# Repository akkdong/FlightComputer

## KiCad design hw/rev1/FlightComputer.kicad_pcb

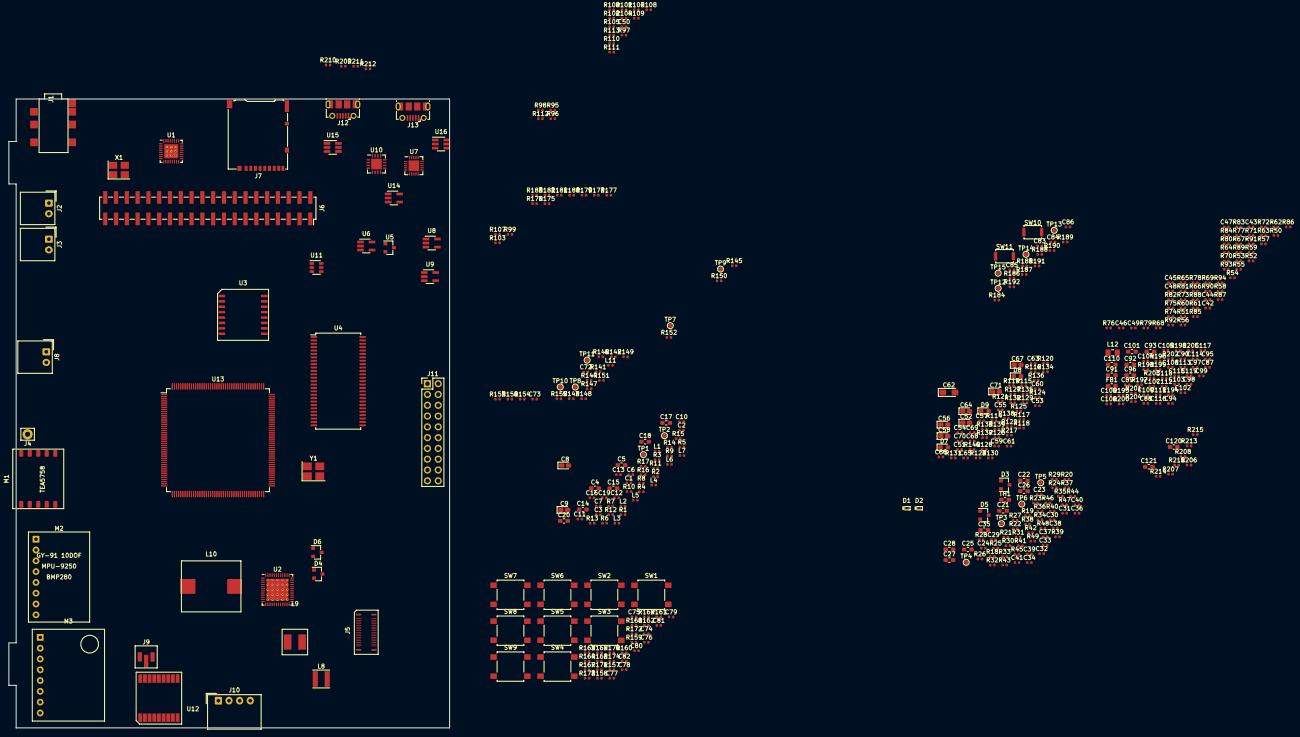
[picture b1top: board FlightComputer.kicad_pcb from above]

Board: 2 copper layers, 103.7 x 148.0 mm, 421 parts (0 on the bottom side), 380 nets, no tracks yet.

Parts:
C1, C2, C3, C16, C19, C41, C42, C43, C44, C45, C46, C47, C48, C49, C50, C51, C57, C63, C68, C70, C73, C74, C75, C76, C77, C78, C79, C80, C81, C82, C85, C86, C87, C88, C89, C94, C98, C100, C102, C103, C104, C105, C106, C107, C108, C109, C111, C112, C113, C114, C115, C116, C117, C118, C119: 0.1uF; C_0402_1005Metric
C4, C5, C14, C15, C91, C92, C93, C110: 4.7uF; C_0603_1608Metric_Pad1.05x0.95mm_HandSolder
C6, C7, C10, C11, C12, C13, C95: 220pF; C_0402_1005Metric
C8, C9, C52, C56, C58, C64, C67, C71: 10uF; CP_EIA-1608-08_AVX-J_Pad1.25x1.05mm_HandSolder
C17, C18, C20, C21, C22, C35, C96, C101, C120, C121: 10uF; C_0603_1608Metric_Pad1.05x0.95mm_HandSolder
C23, C24, C31, C32, C33, C34, C36, C37, C38, C39: 4.7uF; C_0402_1005Metric
C25, C26: 0.1uF; C_0603_1608Metric_Pad1.05x0.95mm_HandSolder
C27, C28: 0.01uF; C_0603_1608Metric_Pad1.05x0.95mm_HandSolder
C29, C30, C61: 2.2uF; C_0402_1005Metric
C40, C53, C54, C59, C65, C69, C90, C97, C99: 1uF; C_0402_1005Metric
C55, C60, C66: N/C; C_0402_1005Metric
C62: 100uF; CP_EIA-3216-10_Kemet-I_Pad1.58x1.35mm_HandSolder
C72: 22pF; C_0402_1005Metric
C83, C84: 18pF; C_0402_1005Metric
D1, D2: BAS3010S; TSLP-2-17
D3, D4, D5, D6: BAT54-SOT23; D_SOT-23_ANK
D7: LED_R; LED_0603_1608Metric_Pad1.05x0.95mm_HandSolder
D8, D9: LED_G; LED_0603_1608Metric_Pad1.05x0.95mm_HandSolder
FB1: BEAD(BMJ1608HM180NTR); L_0603_1608Metric_Pad1.05x0.95mm_HandSolder
J1: SJ-43617-SMT
J2, J3, J8: Conn_01x02; Molex_SPOX_5268-02A_1x02_P2.50mm_Horizontal
J4: Conn_01x01; Pin_D1.2mm_L10.2mm_W2.9mm_FlatFork
J5: ED060SC7_EPD; AXT334124
J6: RPI_Connector; PinSocket_2x20_P2.54mm_Vertical_SMD
J7: Micro_SD_Card; microSD_HC_Hirose_DM3AT-SF-PEJM5
J9: IPEX_IPX; IPEX-IPX
J10: Conn_DEBUG; Molex_SPOX_5268-04A_1x04_P2.50mm_Horizontal
J11: Conn_02x10_Odd_Even; PinHeader_2x10_P2.54mm_Vertical
J12, J13: USB_B_Micro; USB_Micro-B_Molex-105017-0001
L1, L2, L3, L4, L5, L6, L7: Ferrite; L_0402_1005Metric
L8: 2.2uH; L_Taiyo-Yuden_MD-4040
L9: 4.7uH; L_1515(4040 metric)
L10: 68uH w/2A; L_10x11mm
L11: 33nH; L_0402_1005Metric
L12: 2.2uH (LQM2MPN2R2NG0); L_0806_2016Metric
M1: TEA5767_Radio_Module; TEA5756-TJ-102BC
M2: GY-91
M3: GY-86
R1, R113, R116, R120, R123, R127, R133, R136, R161, R162, R163, R164, R169, R170, R171, R172, R174, R175, R176, R183, R186, R188: 100K; R_0402_1005Metric
R2, R3, R4, R5, R6, R7, R8, R9, R10, R13, R15, R16, R17, R23, R24, R25, R26, R27, R28, R29, R32, R33, R34, R35, R38, R39, R40, R41, R42, R43, R44, R45, R47, R48, R49, R50, R51, R52, R53, R54, R55, R56, R57, R58, R59, R60, R61, R62, R63, R64, R65, R66, R67, R68, R69, R70, R71, R72, R73, R74, R75, R76, R77, R78, R79, R80, R81, R82, R83, R84, R85, R86, R87, R88, R89, R90, R91, R92, R93, R94, R97, R98, R99, R100, R101, R102, R107, R108, R109, R110, R111, R112, R122, R124, R126, R131, R135, R141, R142, R143, R144, R145, R146, R147, R150, R151, R152, R153, R154, R155, R156, R177, R178, R179, R180, R181, R182, R206, R209, R210, R211, R212, R213, R214, R215, R216: 33R; R_0402_1005Metric
R11, R12, R117, R148, R149, R185, R193, R195, R198, R199, R200: N/C; R_0402_1005Metric
R14, R30, R31, R36, R37, R46, R184, R189, R190, R191, R192, R207: 10K; R_0402_1005Metric
R18, R20, R115, R128, R140: 1M; R_0402_1005Metric
R19: 47.5K; R_0402_1005Metric
R21: 52.3K; R_0402_1005Metric
R22: 43K; R_0402_1005Metric
R95, R96, R103, R104, R105, R106: 47K; R_0402_1005Metric
R114: 270K; R_0402_1005Metric
R118, R119, R134, R138, R157, R158, R159, R160, R165, R166, R167, R168, R173, R187, R217: 1K; R_0402_1005Metric
R121: 15K; R_0402_1005Metric
R125, R129: 1.87M; R_0402_1005Metric
R130, R132: 340K; R_0402_1005Metric
R137: 560K; R_0402_1005Metric
R139, R194, R196, R197, R201, R202, R203, R204, R205: 0R; R_0402_1005Metric
R208: 47k; R_0402_1005Metric
SW1, SW2, SW3, SW4, SW5, SW6, SW7, SW8, SW9: SW_Push; SW_SPST_B3S-1000
SW10, SW11: SW_Push; SW_Push_SPST_NO_Alps_SKRK
TH1: NCP18XH103F03RB(10K); R_0603_1608Metric_Pad1.05x0.95mm_HandSolder
TP1: OUT3; TestPoint_Pad_D1.0mm
TP2: RINPUT3; TestPoint_Pad_D1.0mm
TP3: EINK_SPI_SCL; TestPoint_Pad_D1.0mm
TP4: EINK_SPI_SDI; TestPoint_Pad_D1.0mm
TP5: EINK_SPI_CS; TestPoint_Pad_D1.0mm
TP6: EINK_SPI_SDO; TestPoint_Pad_D1.0mm
TP7: GPS_SCL; TestPoint_Pad_D1.0mm
TP8: GPS_nRST; TestPoint_Pad_D1.0mm
TP9: GPS_SDA; TestPoint_Pad_D1.0mm
TP10: GPS_WAKEUP; TestPoint_Pad_D1.0mm
TP11: 1PPS; TestPoint_Pad_D1.0mm
TP12: PA1; TestPoint_Pad_D1.0mm
TP13: PC2; TestPoint_Pad_D1.0mm
TP14: PC14; TestPoint_Pad_D1.0mm
TP15: PC15; TestPoint_Pad_D1.0mm
U1: WM8960; QFN-32-1EP_5x5mm_P0.5mm_EP3.3x3.3mm_ThermalVias
U2: TPS65186; VQFN-48-1EP_7x7mm_P0.5mm_EP5.15x5.15mm_ThermalVias
U3: MT25QL512ABB8ESF; SOP2-16_7.5x10.3mm_P1.27mm
U4: MT48LC16M16A2P; TSOP-II-54_22.2x10.16mm_P0.8mm
U5: MAX809TTRG; SOT-23
U6, U8, U9: XC6220B331MR-G; SOT-23-5_HandSoldering
U7: MCP73871; QFN-20-1EP_4x4mm_P0.5mm_EP2.5x2.5mm
U10: TPS61090; QFN-16-1EP_4x4mm_P0.65mm_EP2.5x2.5mm
U11: TPS22917DBV; SOT-23-6
U12: Teseo-LIV3F
U13: STM32H745IIT; LQFP-176_24x24mm_P0.5mm
U14: STMPS2151STR; SOT-23-5_HandSoldering
U15, U16: USBLC6-2SC6; SOT-23-6_Handsoldering
X1: 24MHz; Oscillator_SMD_Abracon_ASE-4Pin_3.2x2.5mm_HandSoldering
Y1: 25MHz; Crystal_SMD_3225-4Pin_3.2x2.5mm_HandSoldering

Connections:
+15V: C33.1, J5.2, J5.4, U2.44
+22V: C29.2, D3.1, J5.25, R18.1
+BATT: C56.1, J8.1, U7.14, U7.15, U7.16
-15V: C34.2, J5.1, J5.3, U2.3
-20V: C30.1, D6.2, J5.27, J5.29, R20.2
/Codec/HPDETECT: J1.4, R9.2
/Codec/I2C_SCL: J6.5, R7.2, R17.2, R96.2
/Codec/I2C_SDA: J6.3, R8.2, R16.2, R95.2
/Codec/I2S_DIN: J6.40, R5.2
/Codec/I2S_LRCK: J6.35, R4.2
/Codec/I2S_MCLK: R2.2, R15.2
/Codec/I2S_SCLK: J6.12, R3.2
/Codec/RADIO_L: C18.2, R10.2, R11.2
/Codec/RADIO_R: C17.2, R12.2, R13.2
/DEBUG/DEBUG_JMS-SWDIO: R179.1, U13.132
/DEBUG/DEBUG_JTCK-SWCLK: R180.1, R183.1, U13.138
/DEBUG/DEBUG_JTDI: R175.2, R178.1, U13.139
/DEBUG/DEBUG_JTDO-SWO: R181.1, U13.162
/DEBUG/DEBUG_nJTRST: R176.2, R177.1, U13.163
/DEBUG/nRST: C85.1, R182.1, R186.1, SW10.1, U13.33
/EINK-PMIC/EPD_CKV: R48.2, U13.101
/EINK-PMIC/EPD_CL: R32.1, U13.102
/EINK-PMIC/EPD_D0: R38.1, U13.145
/EINK-PMIC/EPD_D1: R39.2, U13.146
/EINK-PMIC/EPD_D2: R40.1, U13.147
/EINK-PMIC/EPD_D3: R41.2, U13.148
/EINK-PMIC/EPD_D4: R42.1, U13.149
/EINK-PMIC/EPD_D5: R43.2, U13.150
/EINK-PMIC/EPD_D6: R44.1, U13.94
/EINK-PMIC/EPD_D7: R45.2, U13.95
/EINK-PMIC/EPD_GMODE: R47.2, U13.103
/EINK-PMIC/EPD_LE: R33.2, U13.104
/EINK-PMIC/EPD_OE: R34.1, U13.107
/EINK-PMIC/EPD_PMIC_PWRUP: R26.1, U13.155
/EINK-PMIC/EPD_PMIC_PWR_GOOD: R29.2, U13.156
/EINK-PMIC/EPD_PMIC_SCL: R25.1, R189.2, U13.168
/EINK-PMIC/EPD_PMIC_SDA: R24.1, R190.2, U13.166
/EINK-PMIC/EPD_PMIC_VCOM: R23.1, U13.153
/EINK-PMIC/EPD_PMIC_WAKEUP: R27.1, U13.154
/EINK-PMIC/EPD_PMIC_nINT: R28.2, U13.157
/EINK-PMIC/EPD_SPH: R35.2, U13.108
/EINK-PMIC/EPD_SPV: R49.2, U13.109
/EINK-PMIC/VCOM: C36.1, J5.21, J5.23, U2.14
/EINK_MISO: R100.2, U13.51
/EINK_MOSI: R99.2, U13.52
/EINK_SCLK: R101.2, U13.50
/EINK_nCS: R102.1, U13.49
/IMU1_MISO: R143.2, U13.4
/IMU1_MOSI: R142.2, U13.5
/IMU1_SCLK: R141.2, U13.1
/IMU1_nCS1: R144.2, U13.2
/IMU1_nCS2: R145.2, U13.3
/IMU2_DRDY: R154.2, U13.55
/IMU2_FSYNC: R152.2, U13.56
/IMU2_SCL: R148.1, R150.2, R191.2, U13.78
/IMU2_SDA: R149.1, R151.2, R192.2, U13.79
/IMU2_nINT: R153.2, U13.57
/KEYBOARD/KEY_DOWN: R158.2, U13.123
/KEYBOARD/KEY_ENTER: R165.2, U13.41
/KEYBOARD/KEY_ESCAPE: R166.2, U13.9
/KEYBOARD/KEY_FUNC1: R167.2, U13.124
/KEYBOARD/KEY_FUNC2: R168.2, U13.125
/KEYBOARD/KEY_LEFT: R159.2, U13.53
/KEYBOARD/KEY_RIGHT: R160.2, U13.54
/KEYBOARD/KEY_UP: R157.2, U13.122
/MCU/BAT_SENSING: R139.1, U13.37
/MCU/BOOT0: C86.1, R188.2, SW11.1, U13.167
/MCU/FMC_A0: R51.2, U13.18
/MCU/FMC_A1: R53.2, U13.19
/MCU/FMC_A2: R55.2, U13.20
/MCU/FMC_A3: R57.2, U13.21
/MCU/FMC_A4: R59.2, U13.22
/MCU/FMC_A5: R61.2, U13.23
/MCU/FMC_A6: R63.2, U13.59
/MCU/FMC_A7: R65.2, U13.60
/MCU/FMC_A8: R68.2, U13.61
/MCU/FMC_A9: R71.2, U13.62
/MCU/FMC_A10: R74.2, U13.63
/MCU/FMC_A11: R78.2, U13.66
/MCU/FMC_A12: R81.2, U13.110
/MCU/FMC_BA0: R85.2, U13.114
/MCU/FMC_BA1: R86.2, U13.115
/MCU/FMC_CKE1: R94.2, U13.164
/MCU/FMC_CLK: R93.2, U13.118
/MCU/FMC_D0: R50.1, U13.97
/MCU/FMC_D1: R52.1, U13.98
/MCU/FMC_D2: R54.1, U13.143
/MCU/FMC_D3: R56.1, U13.144
/MCU/FMC_D4: R58.1, U13.67
/MCU/FMC_D5: R60.1, U13.68
/MCU/FMC_D6: R62.1, U13.69
/MCU/FMC_D7: R64.1, U13.72
/MCU/FMC_D8: R67.1, U13.73
/MCU/FMC_D9: R70.1, U13.74
/MCU/FMC_D10: R73.1, U13.75
/MCU/FMC_D11: R77.1, U13.76
/MCU/FMC_D12: R80.1, U13.77
/MCU/FMC_D13: R82.1, U13.89
/MCU/FMC_D14: R83.1, U13.90
/MCU/FMC_D15: R84.1, U13.91
/MCU/FMC_nBL0: R87.2, U13.170
/MCU/FMC_nBL1: R88.2, U13.171
/MCU/FMC_nCAS: R90.2, U13.161
/MCU/FMC_nE1: R92.2, U13.165
/MCU/FMC_nRAS: R91.2, U13.58
/MCU/FMC_nWE: R89.2, U13.34
/MCU/LOW_BATTERY: R131.2, U13.35
/MCU/PWR_5V_EN: R124.1, U13.169
/MCU/PWR_BAT+_EN: R135.1, U13.111
/MCU/PWR_EXTRA_EN: R126.2, U13.158
/MCU/PWR_PERIPH_EN: R122.2, U13.117
/MCU/USB_FS_DN: R216.1, U13.130
/MCU/USB_FS_DP: R215.1, U13.131
/MCU/USB_FS_VBUS: R214.1, U13.142
/MCU/USB_HS_DN: R212.1, U13.87
/MCU/USB_HS_DP: R211.1, U13.88
/MCU/USB_HS_ID: R213.1, U13.85
/MCU/USB_HS_OVCR: R209.1, U13.127
/MCU/USB_HS_PWR_EN: R206.1, U13.96
/MCU/USB_HS_VBUS: R210.1, U13.86
/Memory/NOR_CLK: R79.1, U13.30
/Memory/NOR_DQ0: R66.2, U13.28
/Memory/NOR_DQ1: R69.2, U13.29
/Memory/NOR_DQ2: R72.2, U13.27
/Memory/NOR_DQ3: R76.2, U13.26
/Memory/NOR_nCS: R75.1, U13.116
/Raspberry/I2S_DIN: J6.38, R6.2
/Raspberry/SDIO_CLK: J6.15, R110.2
/Raspberry/SDIO_CMD: J6.16, R104.2, R109.2
/Raspberry/SDIO_DAT0: J6.18, R105.2, R111.2
/Raspberry/SDIO_DAT1: J6.22, R106.2, R112.2
/Raspberry/SDIO_DAT2: J6.37, R103.2, R107.2
/Raspberry/SDIO_DAT3: J6.13, R108.2, R113.1
/VARIO_RX: R97.1, U13.141
/VARIO_TX: R98.1, U13.140
/Vario/EXTERNAL_RX: R155.2, U13.128
/Vario/EXTERNAL_TX: R156.2, U13.129
/Vario/GPS_RX: R147.1, U13.43
/Vario/GPS_TX: R146.1, U13.46
GND: C1.2, C2.2, C3.2, C4.2, C5.2, C6.2, C7.2, C10.2, C11.2, C12.2, C13.2, C14.2, C15.1, C16.1, C19.2, C20.2, C21.2, C22.1, C23.2, C24.1, C25.2, C26.1, C29.1, C30.2, C31.2, C32.1, C33.2, C34.1, C35.2, C36.2, C37.1, C38.1, C39.1, C40.2, C41.2, C42.2, C43.1, C44.1, C45.1, C46.1, C47.1, C48.1, C49.1, C50.1, C51.2, C52.2, C53.2, C54.2, C55.2, C56.2, C57.2, C58.2, C59.2, C60.2, C61.2, C62.2, C63.2, C64.2, C65.2, C66.2, C67.2, C68.2, C69.2, C70.2, C71.2, C72.1, C73.1, C74.2, C75.2, C76.2, C77.2, C78.2, C79.2, C80.2, C81.2, C82.2, C83.2, C84.2, C85.2, C86.2, C87.2, C88.2, C89.2, C90.2, C94.2, C102.2, C103.2, C104.2, C105.2, C106.2, C107.2, C108.2, C109.2, C110.2, C111.2, C112.2, C113.2, C114.2, C115.2, C116.2, C117.2, C118.2, C119.2, C120.2, C121.2, D9.1, J1.1, J5.6, J5.8, J5.31, J5.32, J6.6, J6.9, J6.14, J6.20, J6.25, J6.30, J6.34, J6.39, J7.6, J8.2, J9.2, J9.3, J10.4, J11.4, J11.6, J11.8, J11.10, J11.12, J11.14, J11.16, J11.18, J11.20, J12.5, J12.6, J13.5, J13.6, L9.2, M1.3, M1.6, M1.9, M2.3, M3.3, R19.1, R21.2, R22.1, R113.2, R116.2, R119.2, R120.2, R121.2, R123.1, R127.1, R130.2, R132.2, R133.2, R136.1, R140.1, R161.1, R162.1, R163.1, R164.1, R169.1, R170.1, R171.1, R172.1, R174.1, R183.2, R185.1, R188.1, R204.2, R205.2, R207.2, SW10.2, TH1.2, U1.9, U1.20, U1.24, U1.28, U1.33, U2.6, U2.8, U2.33, U2.41, U2.48, U3.10, U4.6, U4.12, U4.28, U4.41, U4.46, U4.52, U4.54, U5.1, U6.2, U7.10, U7.11, U7.21, U8.2, U9.2, U10.5, U10.6, U10.7, U10.10, U10.13, U10.17, U11.2, U12.1, U12.10, U12.12, U14.2, U15.2, U16.2, X1.2
GNDS: C91.1, C92.1, C93.1, C95.2, C96.2, C101.2, R205.1, U13.6, U13.12, U13.14, U13.24, U13.45, U13.47, U13.64, U13.70, U13.81, U13.83, U13.93, U13.100, U13.106, U13.112, U13.119, U13.134, U13.137, U13.151, U13.159, U13.173
unnamed: C6.1, J1.2, L1.2
unnamed: C7.1, J1.3, L2.2
unnamed: C8.1, U1.31
unnamed: C8.2, L1.1
unnamed: C9.1, U1.29
unnamed: C9.2, L2.1
unnamed: C10.1, J2.1, L3.2
unnamed: C11.1, J2.2, L4.2
unnamed: C12.1, J3.1, L5.2
unnamed: C13.1, J3.2, L6.2
unnamed: C14.1, U1.1
unnamed: C15.2, U1.27
unnamed: C16.2, R14.1, X1.1
unnamed: C17.1, M1.8
unnamed: C18.1, M1.7
unnamed: C19.1, C20.1, L7.2, M1.5
unnamed: C23.1, C31.1, D1.1, U2.37, U2.42, U2.43
unnamed: C24.2, C32.2, C39.2, D2.2, U2.4, U2.16, U2.23, U2.28, U2.29, U2.49
unnamed: C25.1, D4.2, U2.35
unnamed: C26.2, D5.1, U2.31
unnamed: C27.1, U2.36
unnamed: C27.2, D3.2, D4.1
unnamed: C28.1, D5.2, D6.1
unnamed: C28.2, U2.30
unnamed: C37.2, U2.7
unnamed: C38.2, U2.1
unnamed: C53.1, R115.1, U6.3
unnamed: C55.1, U6.4
unnamed: C60.1, U8.4
unnamed: C66.1, U9.4
unnamed: C72.2, L11.1, U12.14
unnamed: C74.1, R157.1, R161.2, SW1.1
unnamed: C75.1, R158.1, R162.2, SW2.1
unnamed: C76.1, R159.1, R163.2, SW3.1
unnamed: C77.1, R160.1, R164.2, SW4.1
unnamed: C78.1, R165.1, R169.2, SW5.1
unnamed: C79.1, R166.1, R170.2, SW6.1
unnamed: C80.1, R167.1, R171.2, SW7.1
unnamed: C81.1, R168.1, R172.2, SW8.1
unnamed: C82.1, R173.1, R174.2, SW9.2
unnamed: C83.1, U13.31, Y1.3
unnamed: C84.1, U13.32, Y1.1
unnamed: C87.1, R195.1
unnamed: C88.1, R196.1
unnamed: C89.1, R197.1
unnamed: C91.2, C92.2, C93.2, L12.1, R194.1, R198.1, R199.1, R200.1, R203.2, U13.17
unnamed: C95.1, L12.2, U13.15
unnamed: C96.1, FB1.2, R193.1, U13.16
unnamed: C97.1, C98.1, R201.1, U13.40
unnamed: C99.1, C100.1, R202.1, U13.39
unnamed: C97.2, C98.2, C99.2, C100.2, R204.1, U13.38
unnamed: C101.1, R203.1
unnamed: C120.1, J12.1, R210.2, U14.1, U15.5
unnamed: D1.2, L8.2, U2.40
unnamed: D2.1, L9.1, U2.25
unnamed: D7.1, R117.1, R217.1
unnamed: D8.1, R118.1
unnamed: D9.2, R138.2
unnamed: J1.12, R1.2
unnamed: J4.1, M1.10
unnamed: J5.9, R32.2
unnamed: J5.10, R33.1
unnamed: J5.11, R34.2
unnamed: J5.12, R35.1
unnamed: J5.13, R38.2
unnamed: J5.14, R39.1
unnamed: J5.15, R40.2
unnamed: J5.16, R41.1
unnamed: J5.17, R42.2
unnamed: J5.18, R43.1
unnamed: J5.19, R44.2
unnamed: J5.20, R45.1
unnamed: J5.22, R36.2, TP3.1
unnamed: J5.24, R37.2, TP4.1
unnamed: J5.26, R47.1
unnamed: J5.28, R48.1
unnamed: J5.30, R49.1
unnamed: J5.33, R46.2, TP5.1
unnamed: J5.34, TP6.1
unnamed: J6.8, R97.2
unnamed: J6.10, R98.2
unnamed: J6.19, R99.1
unnamed: J6.21, R100.1
unnamed: J6.23, R101.1
unnamed: J6.24, R102.2
unnamed: J7.1, R107.1
unnamed: J7.2, R108.1
unnamed: J7.3, R109.1
unnamed: J7.5, R110.1
unnamed: J7.7, R111.1
unnamed: J7.8, R112.1
unnamed: J9.1, L11.2, U12.11
unnamed: J10.2, R155.1
unnamed: J10.3, R156.1
unnamed: J11.3, R177.2
unnamed: J11.5, R178.2
unnamed: J11.7, R179.2
unnamed: J11.9, R180.2
unnamed: J11.13, R181.2
unnamed: J11.15, R182.2
unnamed: J12.2, U15.1
unnamed: J12.3, U15.3
unnamed: J12.4, R213.2
unnamed: J13.2, U16.1
unnamed: J13.3, U16.3
unnamed: L3.1, U1.25
unnamed: L4.1, U1.23
unnamed: L5.1, U1.22
unnamed: L6.1, U1.19
unnamed: L10.2, U10.3, U10.4
unnamed: M1.1, R16.1
unnamed: M1.2, R17.1
unnamed: M2.4, R141.1, R148.2
unnamed: M2.5, R142.1, R149.2
unnamed: M2.6, R143.1
unnamed: M2.7, R144.1
unnamed: M2.8, R145.1
unnamed: M3.4, R150.1
unnamed: M3.5, R151.1
unnamed: M3.6, R152.1
unnamed: M3.7, R153.1
unnamed: M3.8, R154.1
unnamed: R2.1, U1.11
unnamed: R3.1, U1.12
unnamed: R4.1, U1.13, U1.15
unnamed: R5.1, U1.14
unnamed: R6.1, U1.16
unnamed: R7.1, U1.17
unnamed: R8.1, U1.18
unnamed: R9.1, U1.2
unnamed: R10.1, U1.3
unnamed: R11.1, U1.4
unnamed: R12.1, U1.5
unnamed: R13.1, U1.6
unnamed: R15.1, X1.3
unnamed: R18.2, R19.2, U2.34
unnamed: R20.1, R21.1, U2.32
unnamed: R22.2, TH1.1, U2.47
unnamed: R23.2, U2.12
unnamed: R24.2, U2.18
unnamed: R25.2, U2.17
unnamed: R26.2, U2.22
unnamed: R27.2, U2.5
unnamed: R28.1, R30.2, U2.2
unnamed: R29.1, R31.2, U2.24
unnamed: R50.2, U4.2
unnamed: R51.1, U4.23
unnamed: R52.2, U4.4
unnamed: R53.1, U4.24
unnamed: R54.2, U4.5
unnamed: R55.1, U4.25
unnamed: R56.2, U4.7
unnamed: R57.1, U4.26
unnamed: R58.2, U4.8
unnamed: R59.1, U4.29
unnamed: R60.2, U4.10
unnamed: R61.1, U4.30
unnamed: R62.2, U4.11
unnamed: R63.1, U4.31
unnamed: R64.2, U4.13
unnamed: R65.1, U4.32
unnamed: R66.1, U3.15
unnamed: R67.2, U4.42
unnamed: R68.1, U4.33
unnamed: R69.1, U3.8
unnamed: R70.2, U4.44
unnamed: R71.1, U4.34
unnamed: R72.1, U3.9
unnamed: R73.2, U4.45
unnamed: R74.1, U4.22
unnamed: R75.2, U3.7
unnamed: R76.1, U3.1
unnamed: R77.2, U4.47
unnamed: R78.1, U4.35
unnamed: R79.2, U3.16
unnamed: R80.2, U4.48
unnamed: R81.1, U4.36
unnamed: R82.2, U4.50
unnamed: R83.2, U4.51
unnamed: R84.2, U4.53
unnamed: R85.1, U4.20
unnamed: R86.1, U4.21
unnamed: R87.1, U4.15
unnamed: R88.1, U4.39
unnamed: R89.1, U4.16
unnamed: R90.1, U4.17
unnamed: R91.1, U4.18
unnamed: R92.1, U4.19
unnamed: R93.1, U4.38
unnamed: R94.1, U4.37
unnamed: R114.2, R116.1, U7.2
unnamed: R115.2, U5.2
unnamed: R117.2, U7.8
unnamed: R118.2, U7.7
unnamed: R119.1, U7.13
unnamed: R120.1, U7.12
unnamed: R121.1, U7.5
unnamed: R122.1, R123.2, U8.3
unnamed: R124.2, R133.1, U10.11
unnamed: R125.2, R130.1, U10.14
unnamed: R126.1, R127.2, U9.3
unnamed: R128.2, R131.1, U10.12
unnamed: R129.2, R132.1, U10.9
unnamed: R134.1, U11.5
unnamed: R135.2, R136.2, U11.3
unnamed: R137.2, R139.2, R140.2
unnamed: R146.2, U12.2
unnamed: R147.2, U12.3
unnamed: R184.2, R185.2, U13.174
unnamed: R187.1, SW11.2
unnamed: R193.2, R194.2, U13.82, U13.135, U13.175
unnamed: R195.2, R196.2, R197.2, R198.2, R199.2, R200.2, U13.80, U13.133, U13.172
unnamed: R206.2, R207.1, U14.4
unnamed: R208.1, R209.2, U14.3
unnamed: R211.2, U15.4
unnamed: R212.2, U15.6
unnamed: R215.2, U16.4
unnamed: R216.2, U16.6
unnamed: R217.2, U7.6
unnamed: TP1.1, U1.30
unnamed: TP2.1, U1.7
unnamed: TP7.1, U12.17
unnamed: TP8.1, U12.9
unnamed: TP9.1, U12.16
unnamed: TP10.1, U12.5
unnamed: TP11.1, U12.4
unnamed: TP12.1, U13.42
unnamed: TP13.1, U13.36
unnamed: TP14.1, U13.10
unnamed: TP15.1, U13.11
VCC_3V3: C1.1, C2.1, C3.1, C50.2, J6.1, J7.4, L7.1, R1.1, R14.2, R95.1, R96.1, R103.1, R104.1, R105.1, R106.1, U1.8, U1.10, U1.32, X1.4
VCC_5V: C4.1, C5.1, C61.1, C62.1, J6.2, J6.4, R125.1, R128.1, U1.21, U1.26, U10.1, U10.15, U10.16, U14.5
VCC_BAT: C54.1, C59.1, C65.1, C67.1, C68.1, C69.1, L10.1, R129.1, U5.3, U6.1, U7.1, U7.20, U8.1, U9.1, U10.8, U11.1
VCC_BAT+: C21.1, C22.2, C35.1, C70.1, C71.1, L8.1, M2.1, M3.1, R134.2, R137.1, R138.1, U2.10, U2.27, U11.6
VCC_EINK: C40.1, C41.1, J5.5, J5.7, R30.1, R31.1, R36.1, R37.1, R46.1, U2.46
VCC_EXTRA: C63.1, C64.1, U9.5
VCC_MCU: C51.1, C52.1, C90.1, C94.1, C102.1, C103.1, C104.1, C105.1, C106.1, C107.1, C108.1, C109.1, C110.1, C111.1, C112.1, C113.1, C114.1, C115.1, C116.1, C117.1, C118.1, C119.1, FB1.1, J11.1, J11.2, R175.1, R176.1, R184.1, R186.2, R187.2, R189.1, R190.1, R191.1, R192.1, R201.2, R202.2, R208.2, U6.5, U13.7, U13.8, U13.13, U13.25, U13.44, U13.48, U13.65, U13.71, U13.84, U13.92, U13.99, U13.105, U13.113, U13.120, U13.121, U13.126, U13.136, U13.152, U13.160, U13.176
VCC_PERIH: C42.1, C43.2, C44.2, C45.2, C46.2, C47.2, C48.2, C49.2, C57.1, C58.1, C73.2, J10.1, SW1.2, SW2.2, SW3.2, SW4.2, SW5.2, SW6.2, SW7.2, SW8.2, SW9.1, U2.45, U3.2, U4.1, U4.3, U4.9, U4.14, U4.27, U4.43, U4.49, U8.5, U12.6, U12.7, U12.8
VCC_USB: C121.1, D7.2, D8.2, J13.1, R114.1, R214.2, U7.3, U7.4, U7.9, U7.17, U7.18, U7.19, U16.5

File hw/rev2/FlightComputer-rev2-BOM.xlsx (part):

| Noname | Reference(s) | References | Qty | Flag | Value | Package | Manufacturer Part# | LibPart | Footprint | Datasheet
 |  | C27 | C27 | 1 |  | 0.01uF |  |  | Device:C_Small | Capacitor_SMD:C_0603_1608Metric_Pad1.05x0.95mm_HandSolder | ~
 |  | C28 | C27, C28 | 2 | Last | 0.01uF |  |  | Device:C_Small | Capacitor_SMD:C_0603_1608Metric_Pad1.05x0.95mm_HandSolder | ~
 |  | C1 | C1 | 1 |  | 0.1uF |  |  | Device:C_Small | FlightComputer_Library:C_0402_1005Metric_Pad0.74x0.62mm_HandSolder | ~
 |  | C100 | C1, C100 | 2 |  | 0.1uF |  |  | Device:C_Small | FlightComputer_Library:C_0402_1005Metric_Pad0.74x0.62mm_HandSolder | ~
 |  | C1005 | C1, C100, C1005 | 3 |  | 0.1uF |  |  | Device:C_Small | FlightComputer_Library:C_0402_1005Metric_Pad0.74x0.62mm_HandSolder | ~
 |  | C1006 | C1, C100, C1005, C1006 | 4 |  | 0.1uF |  |  | Device:C_Small | FlightComputer_Library:C_0402_1005Metric_Pad0.74x0.62mm_HandSolder | ~
 |  | C1007 | C1, C100, C1005, C1006, C1007 | 5 |  | 0.1uF |  |  | Device:C_Small | FlightComputer_Library:C_0402_1005Metric_Pad0.74x0.62mm_HandSolder | ~
 |  | C1017 | C1, C100, C1005, C1006, C1007, C1017 | 6 |  | 0.1uF |  |  | Device:C_Small | FlightComputer_Library:C_0402_1005Metric_Pad0.74x0.62mm_HandSolder | ~
 |  | C1018 | C1, C100, C1005, C1006, C1007, C1017, C1018 | 7 |  | 0.1uF |  |  | Device:C_Small | FlightComputer_Library:C_0402_1005Metric_Pad0.74x0.62mm_HandSolder | ~
 |  | C1019 | C1, C100, C1005, C1006, C1007, C1017, C1018, C1019 | 8 |  | 0.1uF |  |  | Device:C_Small | FlightComputer_Library:C_0402_1005Metric_Pad0.74x0.62mm_HandSolder | ~
 |  | C102 | C1, C100, C1005, C1006, C1007, C1017, C1018, C1019, C102 | 9 |  | 0.1uF |  |  | Device:C_Small | FlightComputer_Library:C_0402_1005Metric_Pad0.74x0.62mm_HandSolder | ~
 |  | C103 | C1, C100, C1005, C1006, C1007, C1017, C1018, C1019, C102, C103 | 10 |  | 0.1uF |  |  | Device:C_Small | FlightComputer_Library:C_0402_1005Metric_Pad0.74x0.62mm_HandSolder | ~
 |  | C104 | C1, C100, C1005, C1006, C1007, C1017, C1018, C1019, C102, C103, C104 | 11 |  | 0.1uF |  |  | Device:C_Small | FlightComputer_Library:C_0402_1005Metric_Pad0.74x0.62mm_HandSolder | ~
 |  | C105 | C1, C100, C1005, C1006, C1007, C1017, C1018, C1019, C102, C103, C104, C105 | 12 |  | 0.1uF |  |  | Device:C_Small | FlightComputer_Library:C_0402_1005Metric_Pad0.74x0.62mm_HandSolder | ~
 |  | C106 | C1, C100, C1005, C1006, C1007, C1017, C1018, C1019, C102, C103, C104, C105, C106 | 13 |  | 0.1uF |  |  | Device:C_Small | FlightComputer_Library:C_0402_1005Metric_Pad0.74x0.62mm_HandSolder | ~
 |  | C107 | C1, C100, C1005, C1006, C1007, C1017, C1018, C1019, C102, C103, C104, C105, C10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 | 14 |  | 0.1uF |  |  | Device:C_Small | FlightComputer_Library:C_0402_1005Metric_Pad0.74x0.62mm_HandSolder | ~
 |  | C108 | C1, C100, C1005, C1006, C1007, C1017, C1018, C1019, C102, C103, C104, C105, C10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 | 15 |  | 0.1uF |  |  | Device:C_Small | FlightComputer_Library:C_0402_1005Metric_Pad0.74x0.62mm_HandSolder | ~
 |  | C109 | C1, C100, C1005, C1006, C1007, C1017, C1018, C1019, C102, C103, C104, C105, C10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 | 16 |  | 0.1uF |  |  | Device:C_Small | FlightComputer_Library:C_0402_1005Metric_Pad0.74x0.62mm_HandSolder | ~
 |  | C111 | C1, C100, C1005, C1006, C1007, C1017, C1018, C1019, C102, C103, C104, C105, C10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 | 17 |  | 0.1uF |  |  | Device:C_Small | FlightComputer_Library:C_0402_1005Metric_Pad0.74x0.62mm_HandSolder | ~
 |  | C112 | C1, C100, C1005, C1006, C1007, C1017, C1018, C1019, C102, C103, C104, C105, C10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 | 18 |  | 0.1uF |  |  | Device:C_Small | FlightComputer_Library:C_0402_1005Metric_Pad0.74x0.62mm_HandSolder | ~
 |  | C113 | C1, C100, C1005, C1006, C1007, C1017, C1018, C1019, C102, C103, C104, C105, C10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 | 19 |  | 0.1uF |  |  | Device:C_Small | FlightComputer_Library:C_0402_1005Metric_Pad0.74x0.62mm_HandSolder | ~
 |  | C114 | C1, C100, C1005, C1006, C1007, C1017, C1018, C1019, C102, C103, C104, C105, C10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 | 20 |  | 0.1uF |  |  | Device:C_Small | FlightComputer_Library:C_0402_1005Metric_Pad0.74x0.62mm_HandSolder | ~
 |  | C115 | C1, C100, C1005, C1006, C1007, C1017, C1018, C1019, C102, C103, C104, C105, C10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 | 21 |  | 0.1uF |  |  | Device:C_Small | FlightComputer_Library:C_0402_1005Metric_Pad0.74x0.62mm_HandSolder | ~
 |  | C116 | C1, C100, C1005, C1006, C1007, C1017, C1018, C1019, C102, C103, C104, C105, C10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 | 22 |  | 0.1uF |  |  | Device:C_Small | FlightComputer_Library:C_0402_1005Metric_Pad0.74x0.62mm_HandSolder | ~
 |  | C117 | C1, C100, C1005, C1006, C1007, C1017, C1018, C1019, C102, C103, C104, C105, C10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 | 23 |  | 0.1uF |  |  | Device:C_Small | FlightComputer_Library:C_0402_1005Metric_Pad0.74x0.62mm_HandSolder | ~
 |  | C118 | C1, C100, C1005, C1006, C1007, C1017, C1018, C1019, C102, C103, C104, C105, C10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 | 24 |  | 0.1uF |  |  | Device:C_Small | FlightComputer_Library:C_0402_1005Metric_Pad0.74x0.62mm_HandSolder | ~
 |  | C119 | C1, C100, C1005, C1006, C1007, C1017, C1018, C1019, C102, C103, C104, C105, C10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 | 25 |  | 0.1uF |  |  | Device:C_Small | FlightComputer_Library:C_0402_1005Metric_Pad0.74x0.62mm_HandSolder | ~
 |  | C16 | C1, C100, C1005, C1006, C1007, C1017, C1018, C1019, C102, C103, C104, C105, C10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 | 26 |  | 0.1uF |  |  | Device:C_Small | FlightComputer_Library:C_0402_1005Metric_Pad0.74x0.62mm_HandSolder | ~
 |  | C19 | C1, C100, C1005, C1006, C1007, C1017, C1018, C1019, C102, C103, C104, C105, C10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 | 27 |  | 0.1uF |  |  | Device:C_Small | FlightComputer_Library:C_0402_1005Metric_Pad0.74x0.62mm_HandSolder | ~
 |  | C2 | C1, C100, C1005, C1006, C1007, C1017, C1018, C1019, C102, C103, C104, C105, C10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 | 28 |  | 0.1uF |  |  | Device:C_Small | FlightComputer_Library:C_0402_1005Metric_Pad0.74x0.62mm_HandSolder | ~
 |  | C25 | C1, C100, C1005, C1006, C1007, C1017, C1018, C1019, C102, C103, C104, C105, C10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 | 29 |  | 0.1uF |  |  | Device:C_Small | Capacitor_SMD:C_0603_1608Metric_Pad1.05x0.95mm_HandSolder | ~
 |  | C26 | C1, C100, C1005, C1006, C1007, C1017, C1018, C1019, C102, C103, C104, C105, C10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 | 30 |  | 0.1uF |  |  | Device:C_Small | Capacitor_SMD:C_0603_1608Metric_Pad1.05x0.95mm_HandSolder | ~
 |  | C3 | C1, C100, C1005, C1006, C1007, C1017, C1018, C1019, C102, C103, C104, C105, C10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 | 31 |  | 0.1uF |  |  | Device:C_Small | FlightComputer_Library:C_0402_1005Metric_Pad0.74x0.62mm_HandSolder | ~
 |  | C41 | C1, C100, C1005, C1006, C1007, C1017, C1018, C1019, C102, C103, C104, C105, C10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 | 32 |  | 0.1uF |  |  | Device:C_Small | FlightComputer_Library:C_0402_1005Metric_Pad0.74x0.62mm_HandSolder | ~
 |  | C42 | C1, C100, C1005, C1006, C1007, C1017, C1018, C1019, C102, C103, C104, C105, C10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 | 33 |  | 0.1uF |  |  | Device:C_Small | FlightComputer_Library:C_0402_1005Metric_Pad0.74x0.62mm_HandSolder | ~
 |  | C43 | C1, C100, C1005, C1006, C1007, C1017, C1018, C1019, C102, C103, C104, C105, C10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 | 34 |  | 0.1uF |  |  | Device:C_Small | FlightComputer_Library:C_0402_1005Metric_Pad0.74x0.62mm_HandSolder | ~
 |  | C44 | C1, C100, C1005, C1006, C1007, C1017, C1018, C1019, C102, C103, C104, C105, C10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 | 35 |  | 0.1uF |  |  | Device:C_Small | FlightComputer_Library:C_0402_1005Metric_Pad0.74x0.62mm_HandSolder | ~
 |  | C45 | C1, C100, C1005, C1006, C1007, C1017, C1018, C1019, C102, C103, C104, C105, C10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 | 36 |  | 0.1uF |  |  | Device:C_Small | FlightComputer_Library:C_0402_1005Metric_Pad0.74x0.62mm_HandSolder | ~
 |  | C46 | C1, C100, C1005, C1006, C1007, C1017, C1018, C1019, C102, C103, C104, C105, C10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 | 37 |  | 0.1uF |  |  | Device:C_Small | FlightComputer_Library:C_0402_1005Metric_Pad0.74x0.62mm_HandSolder | ~
 |  | C47 | C1, C100, C1005, C1006, C1007, C1017, C1018, C1019, C102, C103, C104, C105, C10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 | 38 |  | 0.1uF |  |  | Device:C_Small | FlightComputer_Library:C_0402_1005Metric_Pad0.74x0.62mm_HandSolder | ~
 |  | C48 | C1, C100, C1005, C1006, C1007, C1017, C1018, C1019, C102, C103, C104, C105, C10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 | 39 |  | 0.1uF |  |  | Device:C_Small | FlightComputer_Library:C_0402_1005Metric_Pad0.74x0.62mm_HandSolder | ~
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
